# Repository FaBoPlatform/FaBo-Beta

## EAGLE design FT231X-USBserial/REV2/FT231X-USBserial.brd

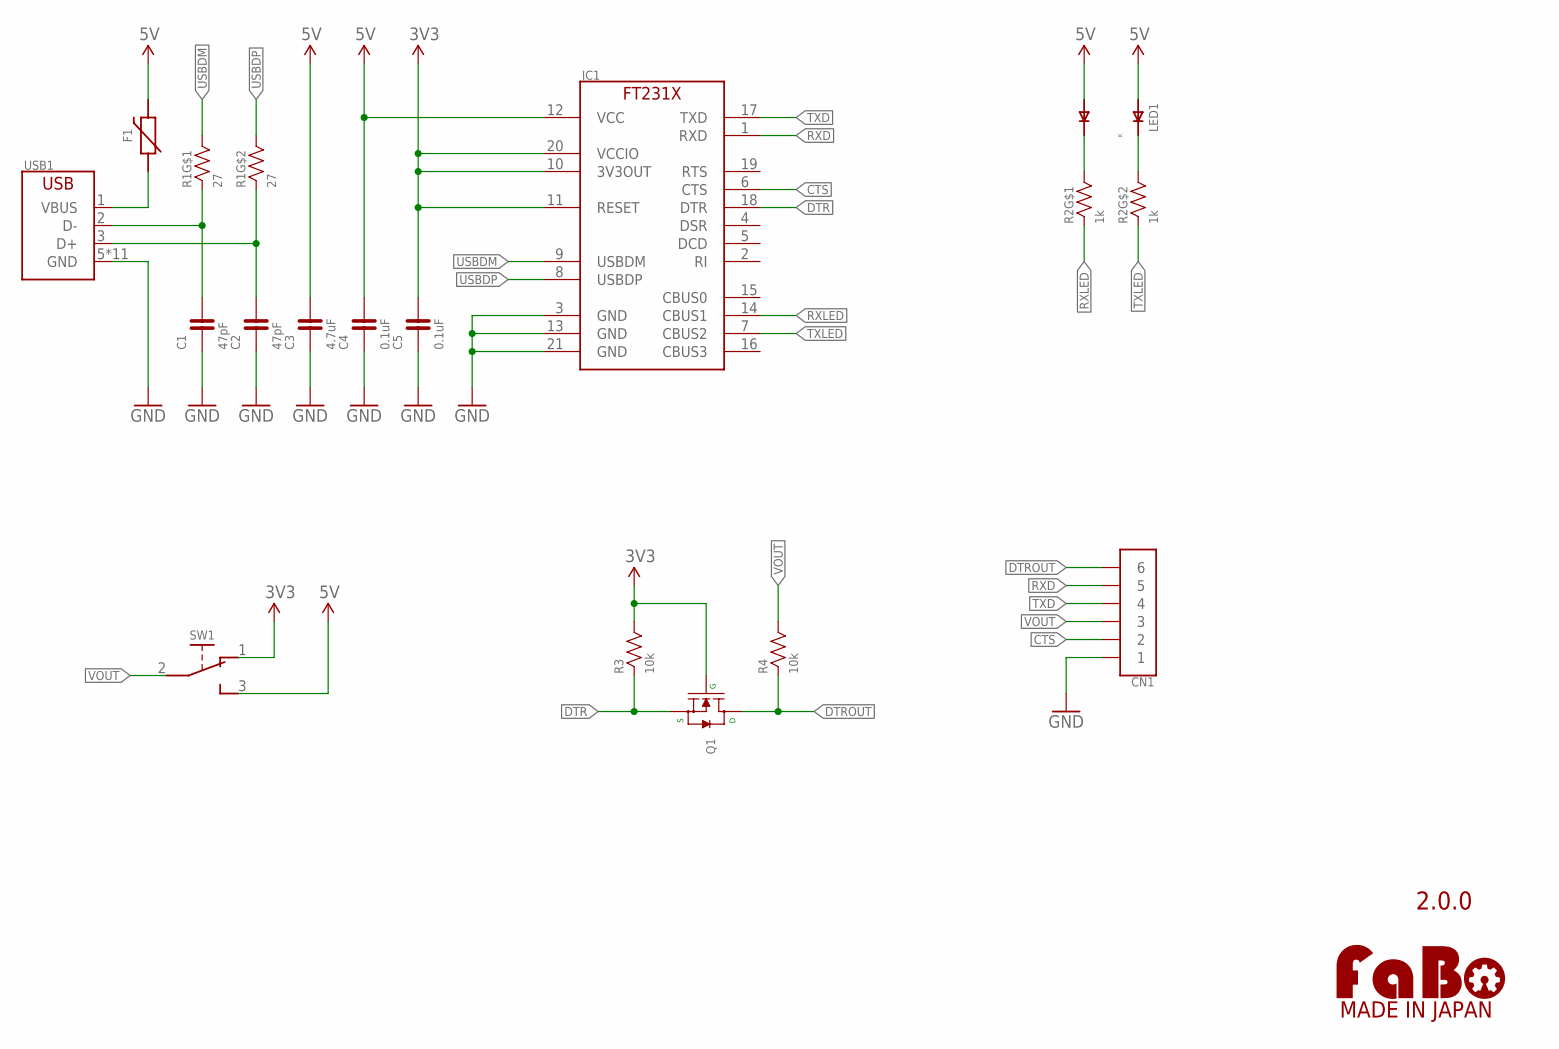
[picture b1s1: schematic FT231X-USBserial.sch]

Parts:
C1, C2: 47pF; EIA0603
C3: 4.7uF; EIA0603
C4, C5: 0.1uF; EIA0603
CN1: PIN_1X6_NARROW
F1: PPTC-NANO; NANOSMDC035F
IC1: FT231XQ; QFN-20
LED1: HSMF-C16X
LOGO1: LOGO_FABO-M_BOTTOM; LOGO_FABO_M_BOTTOM
Q1: MOSFET-N; SOT-23-3
R1: 27; EXBV4V
R2: 1k; EXBV4V
R3, R4: 10k; EIA0603
SW1: SWITCH-SLIDE; SSSS810701
USB1: USB-ZX62D; ZX62D-B-5PA8

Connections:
3V3: C5.2, IC1.10 (3V3OUT), IC1.11 (RESET), IC1.20 (VCCIO), Q1.1 (G), R3.2, SW1.1
5V: C3.2, C4.2, F1.2, IC1.12 (VCC), LED1.1 (A1), LED1.2 (A2), SW1.3
CTS: CN1.2, IC1.6 (CTS)
DTR: IC1.18 (DTR), Q1.2 (S), R3.1
DTROUT: CN1.6, Q1.3 (D), R4.1
GND: C1.1, C2.1, C3.1, C4.1, C5.1, CN1.1, IC1.3 (GND), IC1.13 (GND), IC1.21 (GND), USB1.5 (GND), USB1.B1 (GND), USB1.B2 (GND), USB1.B3 (GND), USB1.B4 (GND), USB1.T1 (GND), USB1.T2 (GND), USB1.T3 (GND), USB1.T4 (GND), USB1.T5 (GND), USB1.T6 (GND)
K_RXLED: LED1.4 (K2), R2.4 (2)
K_TXLED: LED1.3 (K1), R2.3 (2)
O_USBDM: C1.2, R1.1, USB1.2 (D-)
O_USBDP: C2.2, R1.2 (1), USB1.3 (D+)
O_VBUS: F1.1, USB1.1 (VBUS)
RXD: CN1.5, IC1.1 (RXD)
RXLED: IC1.14 (CBUS1), R2.1
TXD: CN1.4, IC1.17 (TXD)
TXLED: IC1.7 (CBUS2), R2.2 (1)
USBDM: IC1.9 (USBDM), R1.4 (2)
USBDP: IC1.8 (USBDP), R1.3 (2)
VOUT: CN1.3, R4.2, SW1.2

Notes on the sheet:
2.0.0

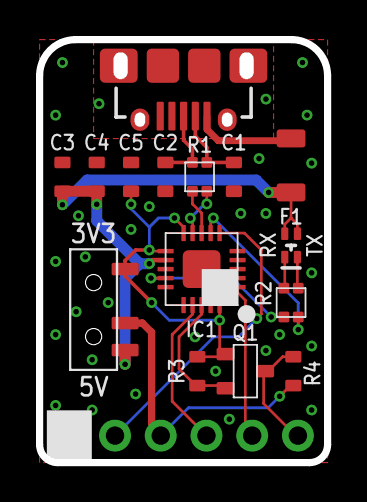
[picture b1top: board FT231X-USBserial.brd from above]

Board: 2 copper layers, 16.0 x 23.5 mm, 17 parts (0 on the bottom side), 18 nets.

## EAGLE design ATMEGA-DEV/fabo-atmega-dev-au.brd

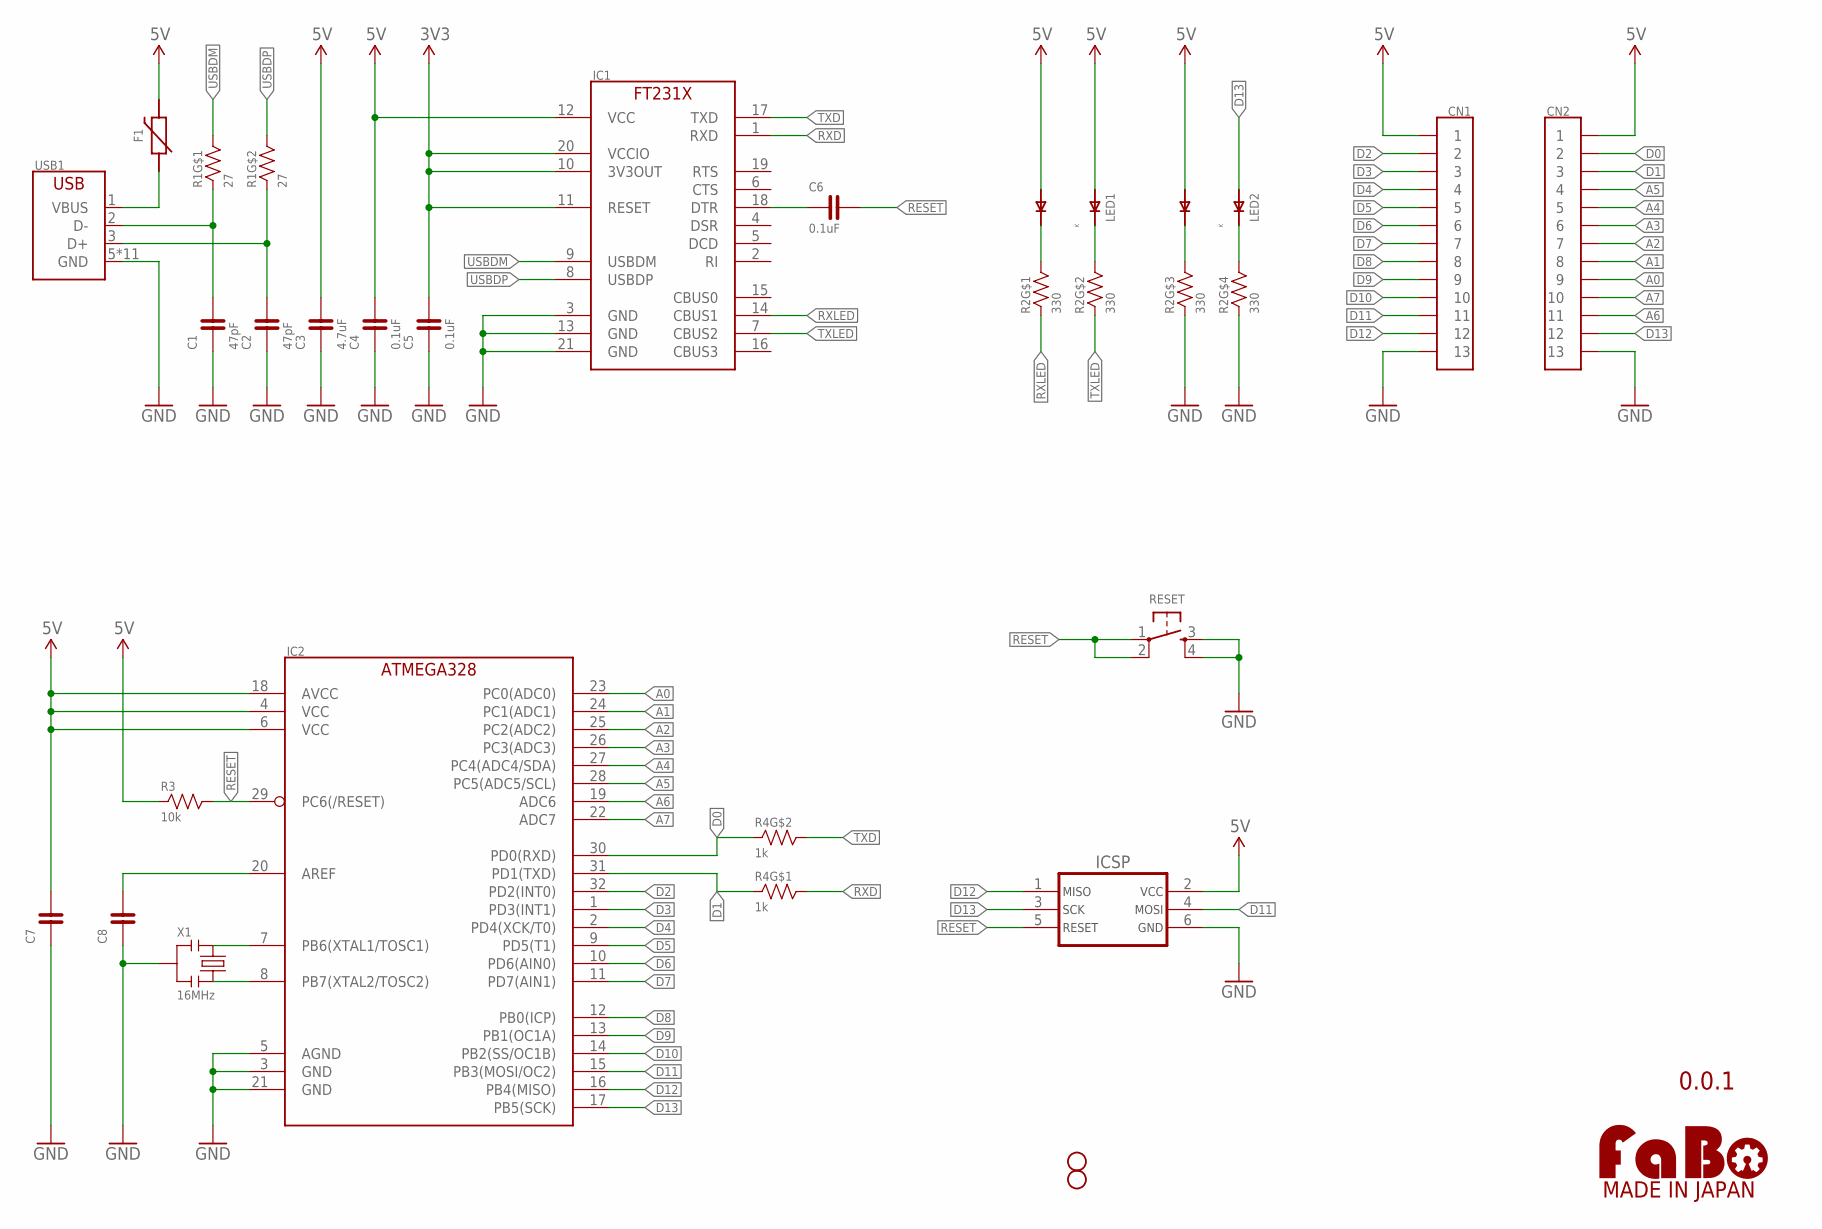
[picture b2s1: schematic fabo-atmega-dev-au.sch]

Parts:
C1, C2: 47pF; EIA0603
C3: 4.7uF; EIA0603
C4, C5, C6: 0.1uF; EIA0603
C7, C8: CAPACITOR-0603; EIA0603
CN1, CN2: PIN_1X13_NARROW
F1: PPTC-NANO; NANOSMDC035F
FID1, FID2: FIDUCIAL-10; FIDUCIAL_10
IC1: FT231XQ; QFN-20
IC2: ATMEGA328P-AU; TQFP-32
ICSP: ICSP_AVR-TC_NOHOLE; TC2030
LED1, LED2: HSMF-C16X
LOGO1: LOGO_FABO-M_BOTTOM; LOGO_FABO_M_BOTTOM
R1: 27; EXBV4V
R2: 330; EXBV8V
R3: 10k; EIA0603
R4: 1k; EXBV4V
RESET: SWITCH-TACTILE-KMR2; KMR2-TACT
USB1: USB-ZX62D; ZX62D-B-5PA8
X1: 16MHz; CSTNE_V_C

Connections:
3V3: C5.2, IC1.10 (3V3OUT), IC1.11 (RESET), IC1.20 (VCCIO)
5V: C3.2, C4.2, C7.2, CN1.1, CN2.1, F1.2, IC1.12 (VCC), IC2.4 (VCC), IC2.6 (VCC), IC2.18 (AVCC), ICSP.2, LED1.1 (A1), LED1.2 (A2), LED2.2 (A2), R3.1
A0: CN2.9, IC2.23 (PC0(ADC0))
A1: CN2.8, IC2.24 (PC1(ADC1))
A2: CN2.7, IC2.25 (PC2(ADC2))
A3: CN2.6, IC2.26 (PC3(ADC3))
A4: CN2.5, IC2.27 (PC4(ADC4/SDA))
A5: CN2.4, IC2.28 (PC5(ADC5/SCL))
A6: CN2.11, IC2.19 (ADC6)
A7: CN2.10, IC2.22 (ADC7)
AREF: C8.2, IC2.20 (AREF)
D0: CN2.2, IC2.30 (PD0(RXD)), R4.2 (1)
D1: CN2.3, IC2.31 (PD1(TXD)), R4.1
D2: CN1.2, IC2.32 (PD2(INT0))
D3: CN1.3, IC2.1 (PD3(INT1))
D4: CN1.4, IC2.2 (PD4(XCK/T0))
D5: CN1.5, IC2.9 (PD5(T1))
D6: CN1.6, IC2.10 (PD6(AIN0))
D7: CN1.7, IC2.11 (PD7(AIN1))
D8: CN1.8, IC2.12 (PB0(ICP))
D9: CN1.9, IC2.13 (PB1(OC1A))
D10: CN1.10, IC2.14 (PB2(SS/OC1B))
D11: CN1.11, IC2.15 (PB3(MOSI/OC2)), ICSP.4
D12: CN1.12, IC2.16 (PB4(MISO)), ICSP.1
D13: CN2.12, IC2.17 (PB5(SCK)), ICSP.3, LED2.1 (A1)
D13LED_K: LED2.3 (K1), R2.5 (2)
DTR: C6.1, IC1.18 (DTR)
GND: C1.1, C2.1, C3.1, C4.1, C5.1, C7.1, C8.1, CN1.13, CN2.13, IC1.3 (GND), IC1.13 (GND), IC1.21 (GND), IC2.3 (GND), IC2.5 (AGND), IC2.21 (GND), ICSP.6, R2.3 (1), R2.4 (1), RESET.3, RESET.4, USB1.5 (GND), USB1.B1 (GND), USB1.B2 (GND), USB1.B3 (GND), USB1.B4 (GND), USB1.T1 (GND), USB1.T2 (GND), USB1.T3 (GND), USB1.T4 (GND), USB1.T5 (GND), USB1.T6 (GND), X1.2
PB6: IC2.7 (PB6(XTAL1/TOSC1)), X1.1
PB7: IC2.8 (PB7(XTAL2/TOSC2)), X1.3
PWRLED_K: LED2.4 (K2), R2.6 (2)
RESET: C6.2, IC2.29 (PC6(/RESET)), ICSP.5, R3.2, RESET.1, RESET.2
RXD: IC1.1 (RXD), R4.4 (2)
RXLED: IC1.14 (CBUS1), R2.1
RXLED_K: LED1.4 (K2), R2.8 (2)
TXD: IC1.17 (TXD), R4.3 (2)
TXLED: IC1.7 (CBUS2), R2.2 (1)
TXLED_K: LED1.3 (K1), R2.7 (2)
USBDM: IC1.9 (USBDM), R1.4 (2)
USBDP: IC1.8 (USBDP), R1.3 (2)
USB_DM: C1.2, R1.1, USB1.2 (D-)
USB_DP: C2.2, R1.2 (1), USB1.3 (D+)
USB_VBUS: F1.1, USB1.1 (VBUS)

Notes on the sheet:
0.0.1

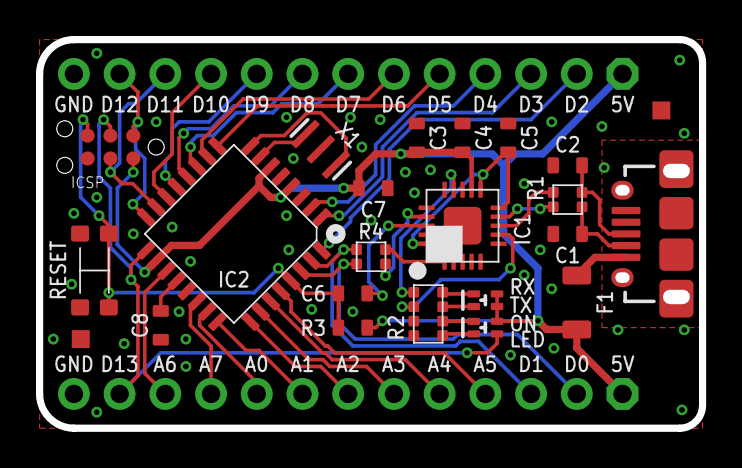
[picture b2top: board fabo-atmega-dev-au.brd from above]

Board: 2 copper layers, 36.8 x 21.6 mm, 26 parts (0 on the bottom side), 43 nets.

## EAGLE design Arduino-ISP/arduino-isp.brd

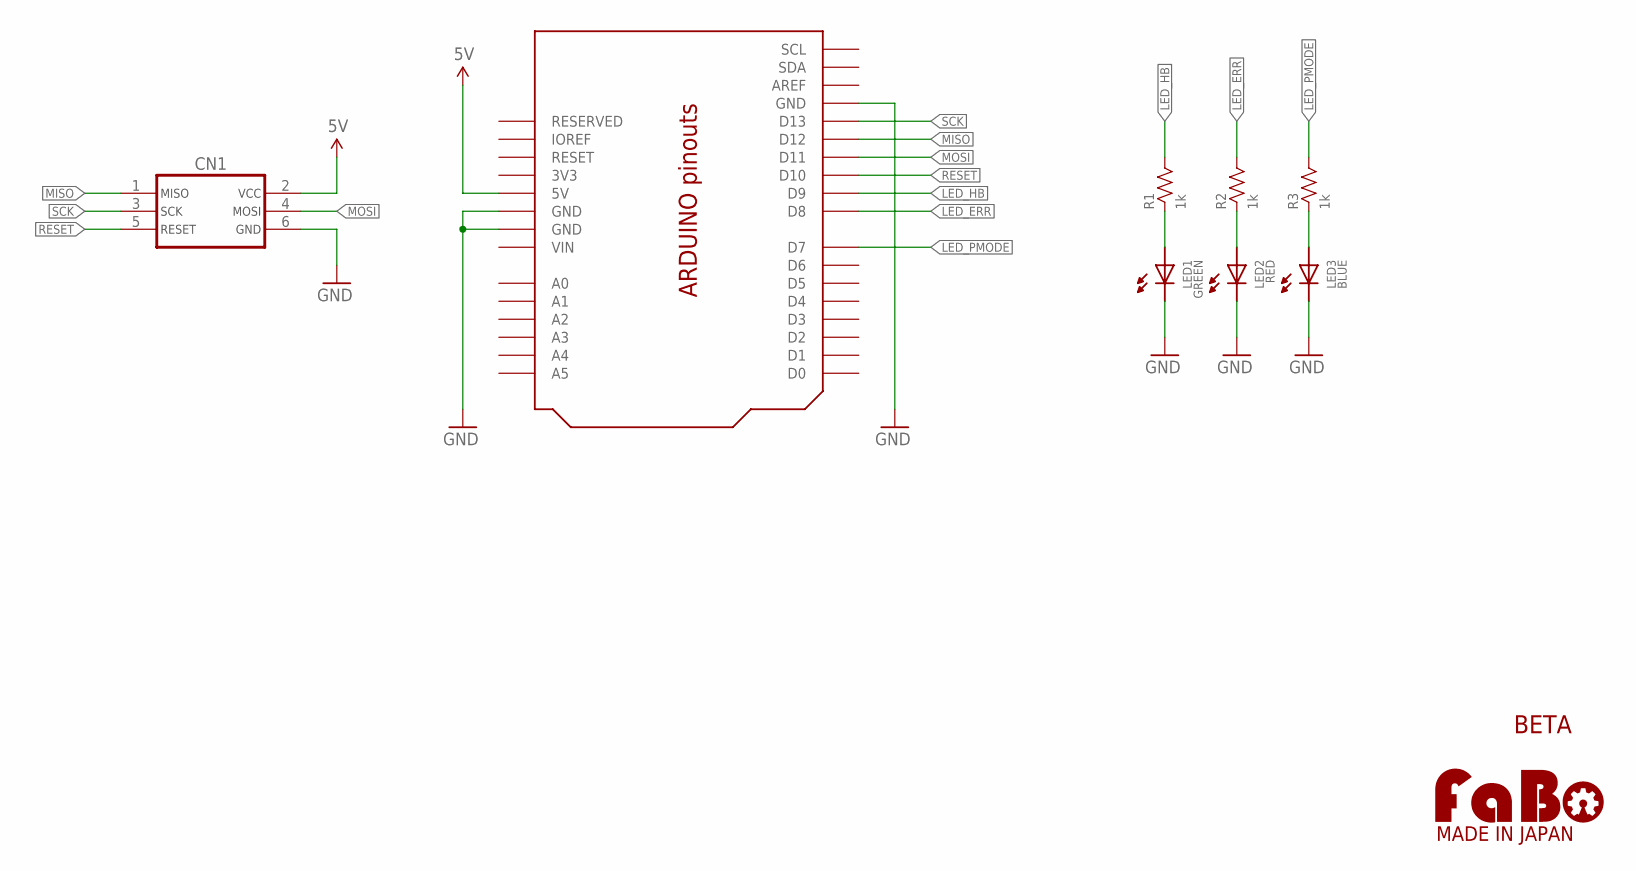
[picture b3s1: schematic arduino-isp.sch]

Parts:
CN1: AVR_ISP_BOX; BOX_2X3
LED1: GREEN; LED_5MM
LED2: RED; LED_5MM
LED3: BLUE; LED_5MM
R1, R2, R3: 1k; AXL-REGULAR
U1: ARDUINO_UNO_R3_SHIELD-HALF; ARDUINO_SHIELD_HALF
U$2: LOGO_FABO-M; LOGO_FABO_MS

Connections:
3V3: U1.3V3
5V: CN1.2, U1.5V
GND: CN1.6, LED1.K (CATHODE), LED2.K (CATHODE), LED3.K (CATHODE), U1.GND1 (GND), U1.GND2 (GND), U1.GND3 (GND)
LED_ERR: R2.2, U1.D8
LED_HB: R1.2, U1.D9
LED_PMODE: R3.2, U1.D7
MISO: CN1.1, U1.D12
MOSI: CN1.4, U1.D11
unnamed: LED1.A (ANODE), R1.1
unnamed: LED2.A (ANODE), R2.1
unnamed: LED3.A (ANODE), R3.1
RESET: CN1.5, U1.D10
SCK: CN1.3, U1.D13
VIN: U1.VIN

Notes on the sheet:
BETA

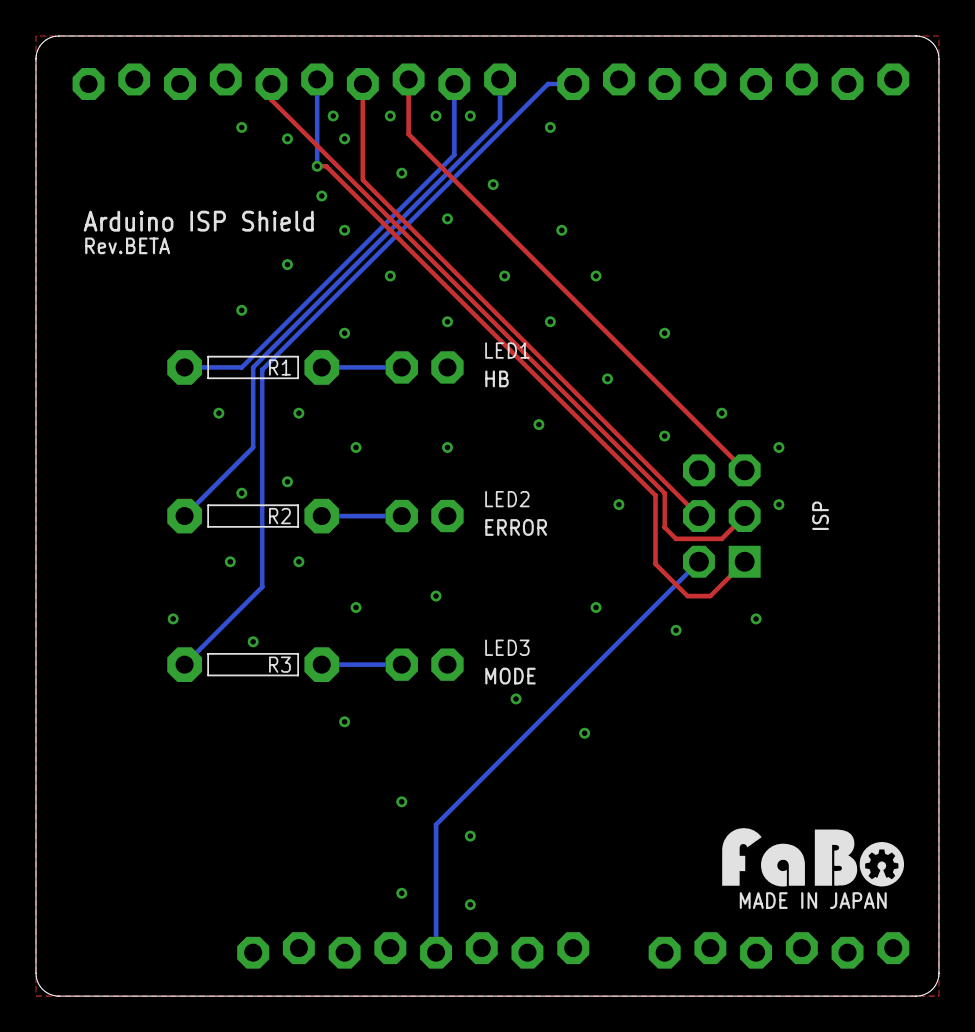
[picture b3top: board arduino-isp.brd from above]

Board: 2 copper layers, 50.2 x 53.3 mm, 9 parts (0 on the bottom side), 12 nets.

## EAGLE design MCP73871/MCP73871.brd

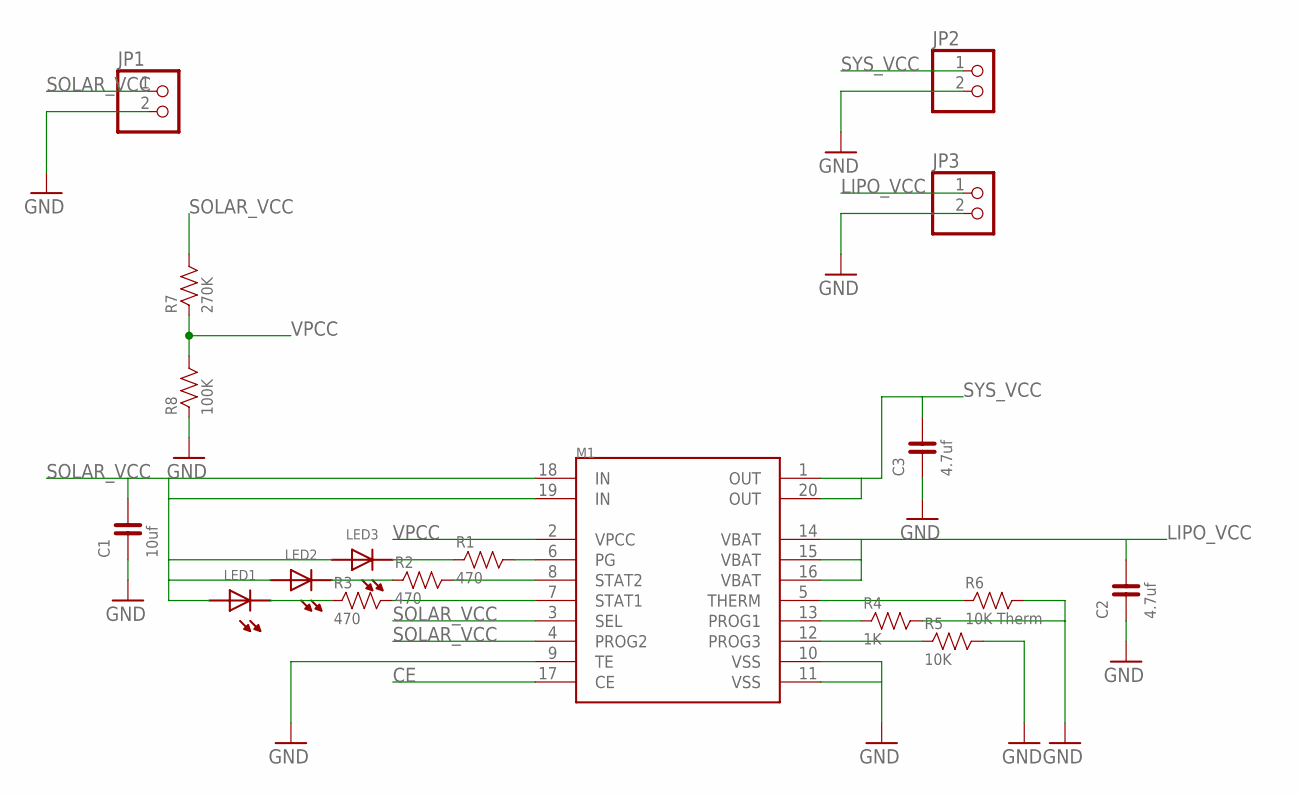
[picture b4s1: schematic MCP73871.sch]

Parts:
C1: 10uf; 0603
C2, C3: 4.7uf; 0603
JP1, JP2, JP3: PINHD-1X2; 1X02
LED1, LED2, LED3: LED-0603; 0603
M1: MCP73871; QFN
R1, R2, R3: 470; 0603
R4: 1K; 0603
R5: 10K; 0603
R6: 10K Therm; 0603
R7: 270K; 0603
R8: 100K; 0603

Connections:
CE: M1.17 (CE)
GND: C1.1, C2.1, C3.1, JP1.2, JP2.2, JP3.2, M1.9 (TE), M1.10 (VSS), M1.11 (VSS), R4.2, R5.2, R6.2, R8.1
LIPO_VCC: C2.2, JP3.1, M1.14 (VBAT), M1.15 (VBAT), M1.16 (VBAT)
unnamed: LED3.CATHODE, R1.1
unnamed: LED2.CATHODE, R2.1
unnamed: M1.5 (THERM), R6.1
unnamed: M1.13 (PROG1), R4.1
unnamed: LED1.CATHODE, R3.1
unnamed: M1.12 (PROG3), R5.1
unnamed: M1.6 (PG), R1.2
unnamed: M1.8 (STAT2), R2.2
unnamed: M1.7 (STAT1), R3.2
SOLAR_VCC: C1.2, JP1.1, LED1.ANODE, LED2.ANODE, LED3.ANODE, M1.3 (SEL), M1.4 (PROG2), M1.18 (IN), M1.19 (IN), R7.2
SYS_VCC: C3.2, JP2.1, M1.1 (OUT), M1.20 (OUT)
VPCC: M1.2 (VPCC), R7.1, R8.2

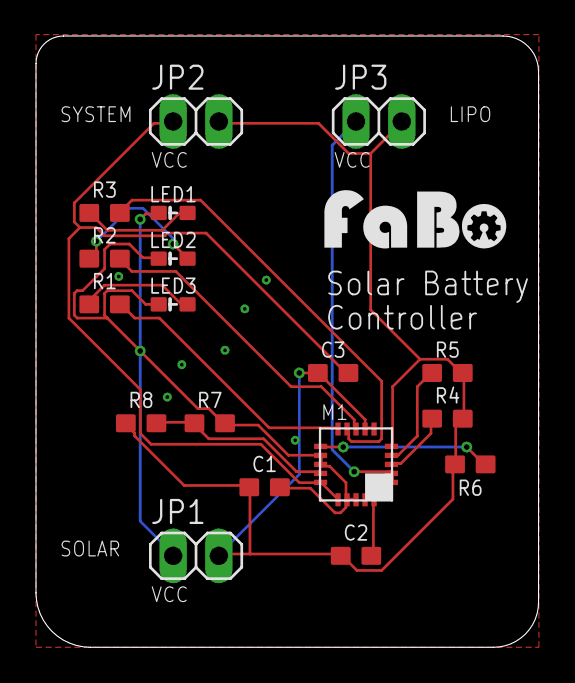
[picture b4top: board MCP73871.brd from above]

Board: 2 copper layers, 27.9 x 34.0 mm, 19 parts (0 on the bottom side), 14 nets.

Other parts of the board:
U$1: LOGO_FABO_MS

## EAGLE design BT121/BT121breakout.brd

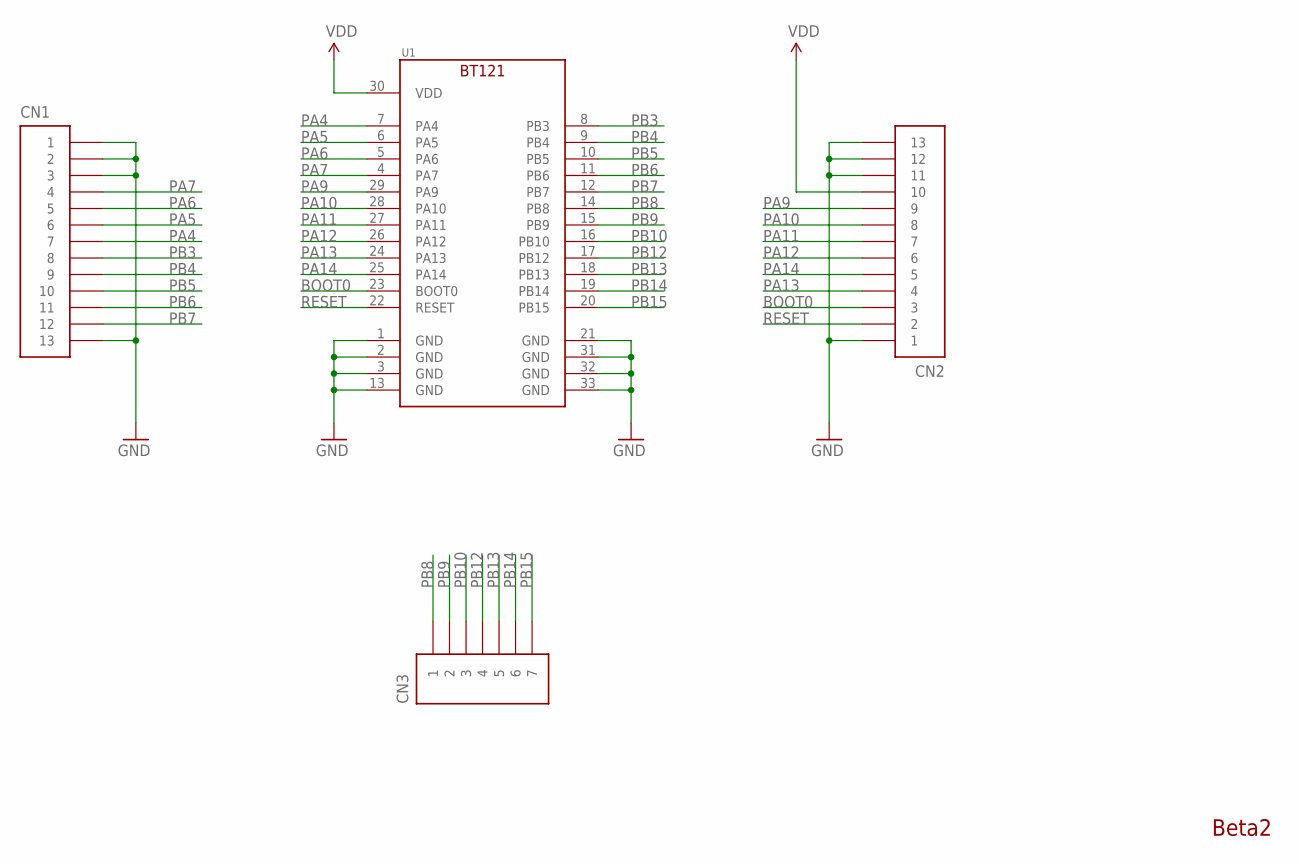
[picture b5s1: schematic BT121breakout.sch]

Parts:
CN1, CN2: PIN_HEADER_1X13; PIN_1X13
CN3: PIN_HEADER_1X7; PIN_1X7
U1: SILICONLABS-BT121

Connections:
BOOT0: CN2.3, U1.23 (BOOT0)
GND: CN1.1, CN1.2, CN1.3, CN1.13, CN2.1, CN2.11, CN2.12, CN2.13, U1.1 (GND), U1.2 (GND), U1.3 (GND), U1.13 (GND), U1.21 (GND), U1.31 (GND), U1.32 (GND), U1.33 (GND)
PA4: CN1.7, U1.7 (PA4)
PA5: CN1.6, U1.6 (PA5)
PA6: CN1.5, U1.5 (PA6)
PA7: CN1.4, U1.4 (PA7)
PA9: CN2.9, U1.29 (PA9)
PA10: CN2.8, U1.28 (PA10)
PA11: CN2.7, U1.27 (PA11)
PA12: CN2.6, U1.26 (PA12)
PA13: CN2.4, U1.24 (PA13)
PA14: CN2.5, U1.25 (PA14)
PB3: CN1.8, U1.8 (PB3)
PB4: CN1.9, U1.9 (PB4)
PB5: CN1.10, U1.10 (PB5)
PB6: CN1.11, U1.11 (PB6)
PB7: CN1.12, U1.12 (PB7)
PB8: CN3.1, U1.14 (PB8)
PB9: CN3.2, U1.15 (PB9)
PB10: CN3.3, U1.16 (PB10)
PB12: CN3.4, U1.17 (PB12)
PB13: CN3.5, U1.18 (PB13)
PB14: CN3.6, U1.19 (PB14)
PB15: CN3.7, U1.20 (PB15)
RESET: CN2.2, U1.22 (RESET)
VDD: CN2.10, U1.30 (VDD)

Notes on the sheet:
Beta2

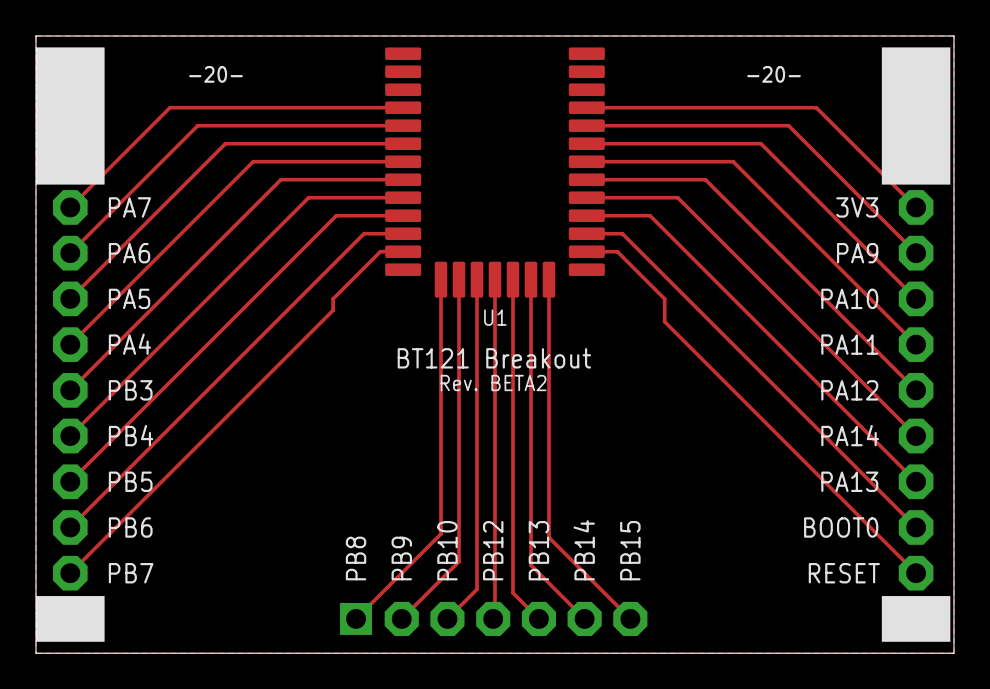
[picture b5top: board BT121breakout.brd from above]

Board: 2 copper layers, 51.0 x 34.3 mm, 4 parts (0 on the bottom side), 26 nets.

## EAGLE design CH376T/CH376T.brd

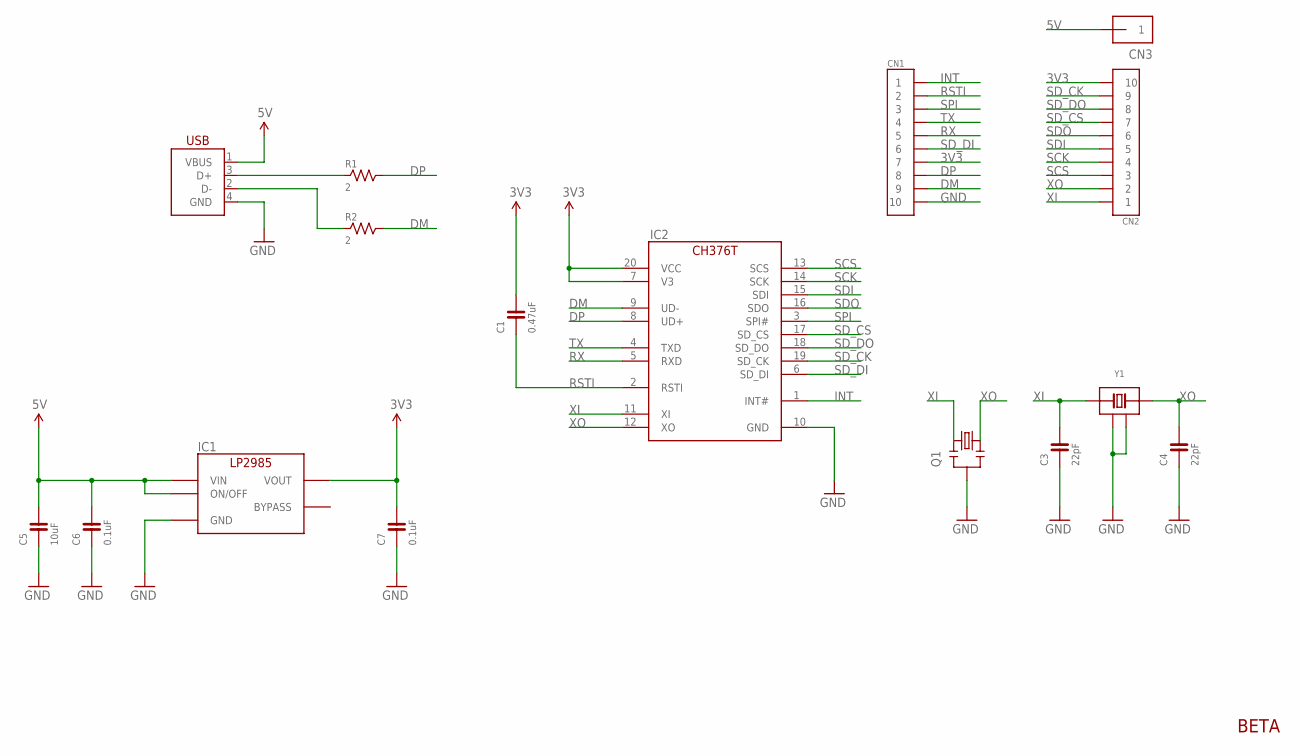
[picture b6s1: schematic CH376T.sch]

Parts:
C1: 0.47uF; 0603-NARROW
C3, C4: 22pF; 0603-NARROW
C5: 10uF; 0603-NARROW
C6, C7: 0.1uF; 0603-NARROW
CN1, CN2: PIN_HEADER_1X10; PIN_1X10
CN3: PIN_HEADER_1X1; PIN_1X1
IC1: LP2985-33DBV; SOT-23-5
IC2: CH376T; SSOP-20
Q1: RESONATOR-CSTCE_G; CSTCE_G
R1, R2: 2; 0603-NARROW
USB1: USB-B_PTH; USB-4AF103BS
Y1: CRYSTAL-ECS-120-12-33Q; ECS-12MHZ

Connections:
3V3: C1.2, C7.2, CN1.7, CN2.10, IC1.5 (VOUT), IC2.7 (V3), IC2.20 (VCC)
5V: C5.2, C6.2, CN3.1, IC1.1 (VIN), IC1.3 (ON/OFF), USB1.1 (VBUS)
DM: CN1.9, IC2.9 (UD-), R2.2
DP: CN1.8, IC2.8 (UD+), R1.2
GND: C3.1, C4.1, C5.1, C6.1, C7.1, CN1.10, IC1.2 (GND), IC2.10 (GND), Q1.2, USB1.4 (GND), Y1.2 (GND), Y1.4 (GND)
INT: CN1.1, IC2.1 (INT#)
unnamed: R1.1, USB1.3 (D+)
unnamed: R2.1, USB1.2 (D-)
RSTI: C1.1, CN1.2, IC2.2 (RSTI)
RX: CN1.5, IC2.5 (RXD)
SCK: CN2.4, IC2.14 (SCK)
SCS: CN2.3, IC2.13 (SCS)
SDI: CN2.5, IC2.15 (SDI)
SDO: CN2.6, IC2.16 (SDO)
SD_CK: CN2.9, IC2.19 (SD_CK)
SD_CS: CN2.7, IC2.17 (SD_CS)
SD_DI: CN1.6, IC2.6 (SD_DI)
SD_DO: CN2.8, IC2.18 (SD_DO)
SPI: CN1.3, IC2.3 (SPI#)
TX: CN1.4, IC2.4 (TXD)
XI: C3.2, CN2.1, IC2.11 (XI), Q1.1, Y1.1 (IO)
XO: C4.2, CN2.2, IC2.12 (XO), Q1.3, Y1.3 (IO)

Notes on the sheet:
BETA

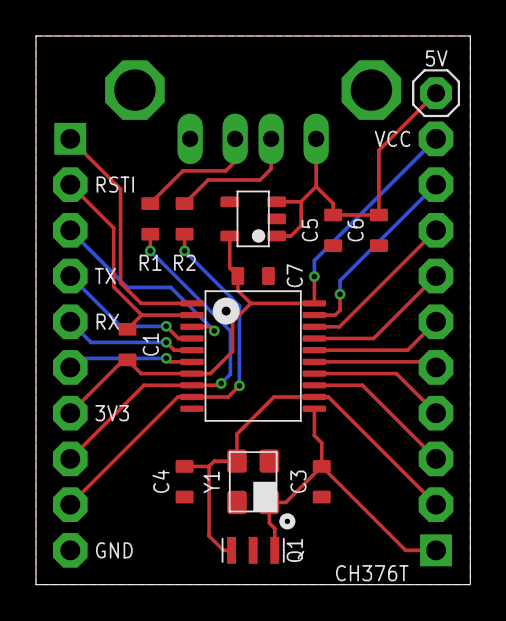
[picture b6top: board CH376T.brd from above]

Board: 2 copper layers, 24.1 x 30.5 mm, 16 parts (0 on the bottom side), 22 nets.

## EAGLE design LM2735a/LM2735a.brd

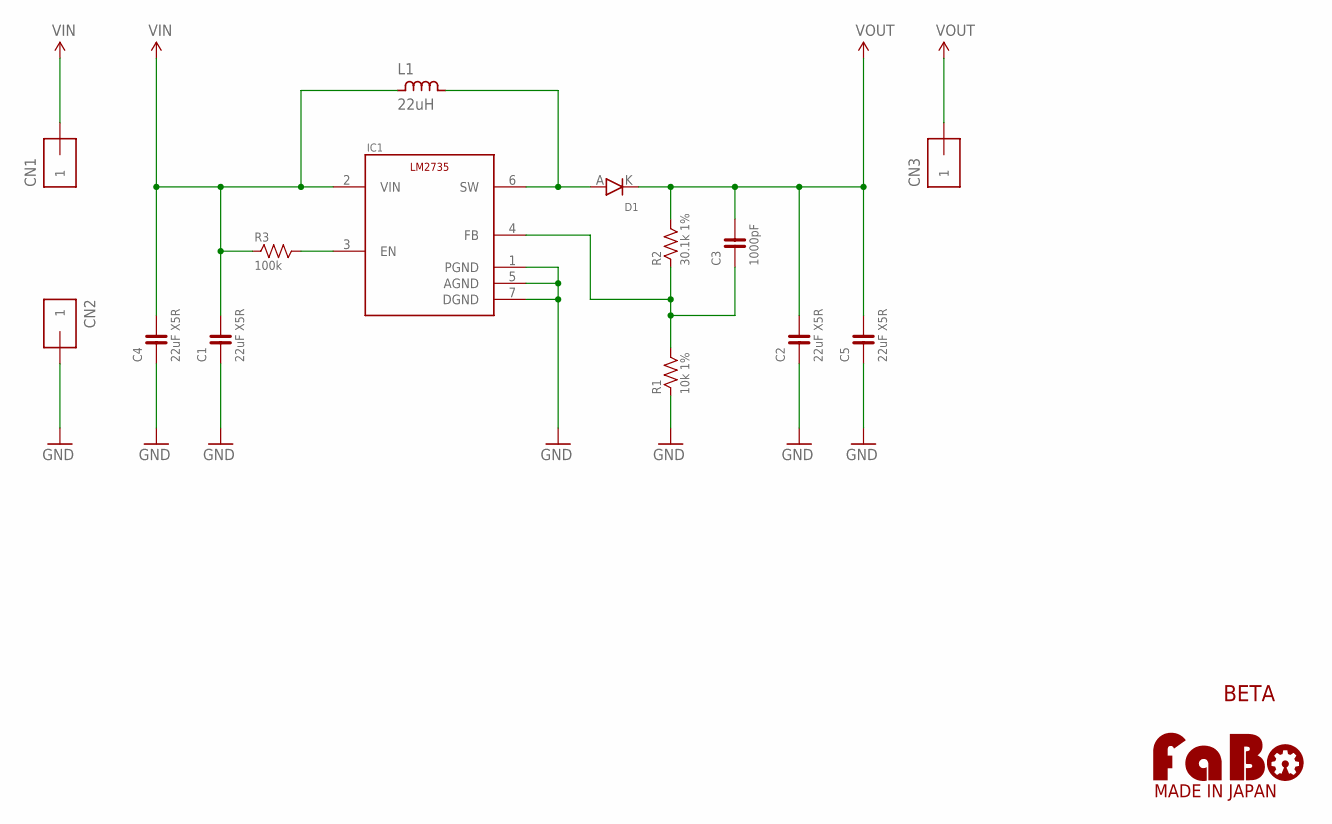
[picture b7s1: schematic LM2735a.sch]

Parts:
C1, C2, C4, C5: 22uF X5R; 0603-NARROW
C3: 1000pF; 0603-NARROW
CN1, CN2, CN3: PIN_HEADER_1X1-SMALL; PIN_1X1_SMALL
D1: DIODE-STPS120M; ST-MITE
IC1: LM2735YQSDX; WSON-6
L1: 22uH; NR5040
R1: 10k 1%; 0603-NARROW
R2: 30.1k 1%; 0603-NARROW
R3: 100k; 0603-NARROW
U$2: LOGO_FABO-M_BOTTOM; LOGO_FABO_MS_BOTTOM

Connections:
FB: C3.1, IC1.4 (FB), R1.2, R2.1
GND: C1.1, C2.1, C4.1, C5.1, CN2.1, IC1.1 (PGND), IC1.5 (AGND), IC1.7 (DGND), R1.1
unnamed: IC1.3 (EN), R3.2
SW: D1.A, IC1.6 (SW), L1.2
VIN: C1.2, C4.2, CN1.1, IC1.2 (VIN), L1.1, R3.1
VOUT: C2.2, C3.2, C5.2, CN3.1, D1.K, R2.2

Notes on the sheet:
BETA

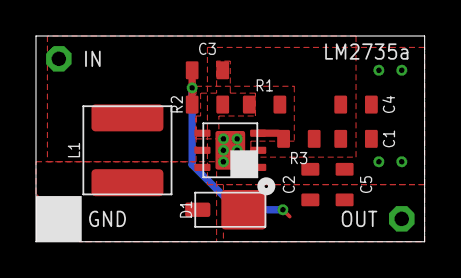
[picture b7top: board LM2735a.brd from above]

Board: 2 copper layers, 21.6 x 11.4 mm, 15 parts (0 on the bottom side), 6 nets.

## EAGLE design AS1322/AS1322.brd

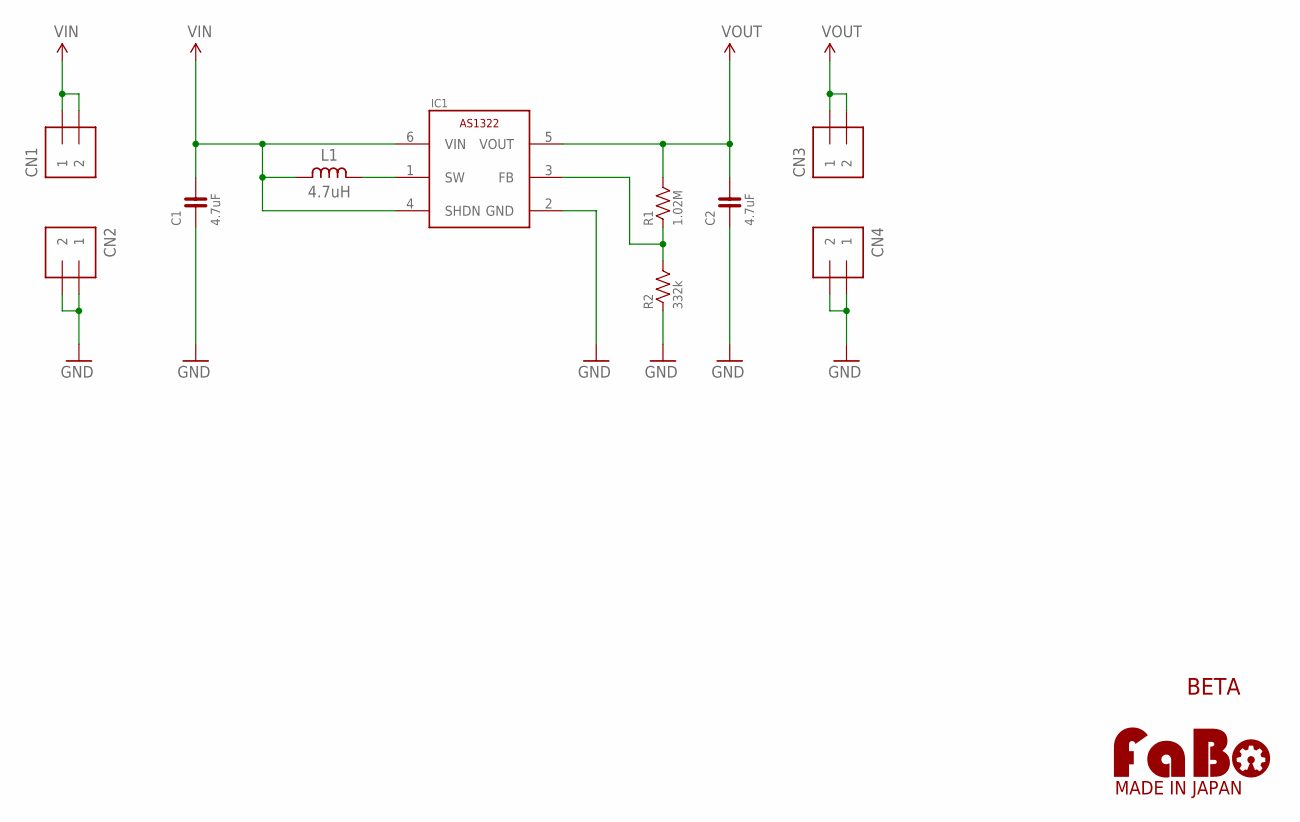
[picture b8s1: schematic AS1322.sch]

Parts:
C1, C2: 4.7uF; 0603-NARROW
CN1, CN2, CN3, CN4: PIN_HEADER_1X2; PIN_1X2
IC1: AS1322; TSOT-23-6
L1: 4.7uH; LQH3NPN
R1: 1.02M; 0603-NARROW
R2: 332k; 0603-NARROW
U$2: LOGO_FABO-M_BOTTOM; LOGO_FABO_MS_BOTTOM

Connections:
GND: C1.1, C2.1, CN2.1, CN2.2, CN4.1, CN4.2, IC1.2 (GND), R2.1
unnamed: IC1.1 (SW), L1.2
VFB: IC1.3 (FB), R1.1, R2.2
VIN: C1.2, CN1.1, CN1.2, IC1.4 (SHDN), IC1.6 (VIN), L1.1
VOUT: C2.2, CN3.1, CN3.2, IC1.5 (VOUT), R1.2

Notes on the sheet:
BETA

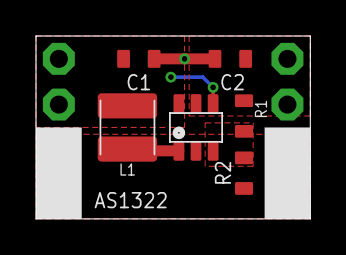
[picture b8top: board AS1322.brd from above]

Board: 2 copper layers, 15.2 x 10.2 mm, 11 parts (0 on the bottom side), 5 nets.

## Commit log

2015-11-09 Add sensors
2015-11-10 Add breakout board
2015-11-10 Add VEML6040, VEML6070
2015-11-11 Update BLE Breakout
2015-11-26 Add update
2016-01-04 Update new meme.
2016-01-29 add PCA9532
2016-03-02 add FT231X breakout
2016-03-02 add BSS138LevelShift
2016-03-15 add PCA9622DR/PCA9955BTW 16bit LED Driver
2016-03-16 add LSF0204RGYR / 4bit voltage level translator
2016-06-05 add PCA9306 i2c level shift ic
2016-07-07 add VNC2 breakout
2016-07-07 fix dimension
2016-07-21 add VNC1
2016-08-23 draft STM32 breakout
2016-08-24 fix STM32F446RET-Breakout Rev.BETA
2016-09-01 add MAX3221EEAE
2016-09-12 change FT231X
2016-09-14 add TPS63000
2016-10-18 add dc-dc
2016-10-21 add LM2735
2016-11-07 add CH376
2016-11-08 add resister
2017-04-04 add FT231X-USBserial
2017-05-09 add BT121 breakout
2017-05-15 chg silk
2017-06-12 change bt121
2017-06-14 Update MDBT40.
2017-12-27 Update.
2018-12-07 add Arduino ISP shield
2018-12-28 restore FT231X
2019-01-11 add FT231X-USBserial/REV2

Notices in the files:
parts and their libraries:
FaBo-Capacitor: Released under the Creative Commons Attribution-ShareAlike 4.0 License
https://creativecommons.org/licenses/by-sa/4.0
FaBo-etc: Released under the Creative Commons
